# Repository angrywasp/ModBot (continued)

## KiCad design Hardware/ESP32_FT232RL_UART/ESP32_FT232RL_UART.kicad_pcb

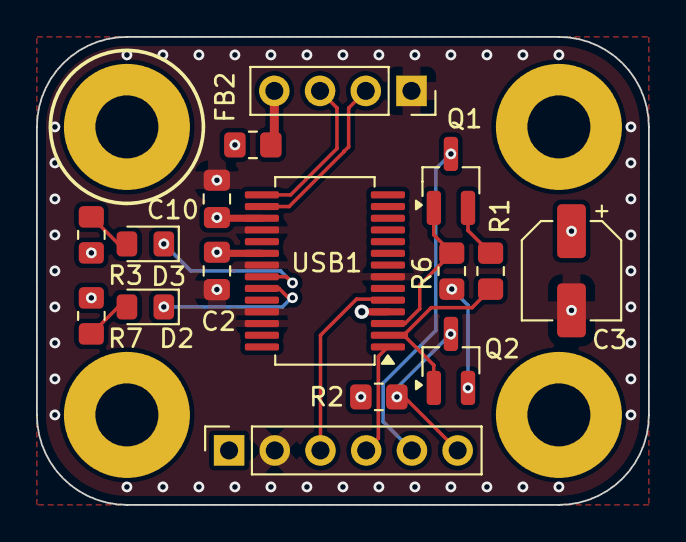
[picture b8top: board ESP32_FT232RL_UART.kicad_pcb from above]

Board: 4 copper layers, 34.0 x 26.0 mm, 16 parts (0 on the bottom side), 18 nets.

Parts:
C2, C10: 0.1uF; C_0805_2012Metric_Pad1.18x1.45mm_HandSolder
C3: 47uF; CP_Elec_5x5.3
D2: BLUE; LED_0805_2012Metric_Pad1.15x1.40mm_HandSolder
D3: RED; LED_0805_2012Metric_Pad1.15x1.40mm_HandSolder
FB2: 220; R_0805_2012Metric_Pad1.20x1.40mm_HandSolder
J1: Conn_01x06; PinSocket_1x06_P2.54mm_Vertical
J2: Conn_01x04; PinSocket_1x04_P2.54mm_Vertical
Q1, Q2: NPN; SOT-23_Handsoldering
R1, R2, R6: 10k; R_0805_2012Metric_Pad1.20x1.40mm_HandSolder
R3, R7: 330; R_0805_2012Metric_Pad1.20x1.40mm_HandSolder
USB1: FT232L; SSOP-28_5.3x10.2mm_P0.65mm

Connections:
+3.3V: C10.2, R2.2, USB1.4 (VCCIO), USB1.17 (3V3OUT)
+5V: C2.2, C3.1, FB2.2, J1.1, R3.1, R7.2, USB1.20 (VCC)
DTR: Q2.1 (E), R1.1, USB1.2 (DTR)
EN: J1.5, Q1.3 (C)
GND: C2.1, C3.2, C10.1, J1.2, J2.1, USB1.7 (GND), USB1.18 (GND), USB1.21 (GND), USB1.25 (AGND), USB1.26 (TEST)
IO0: J1.6, Q2.3 (C), R2.1
unnamed: D2.2 (A), R7.1
unnamed: D2.1 (K), USB1.23 (CBUS0)
unnamed: D3.2 (A), R3.2
unnamed: D3.1 (K), USB1.22 (CBUS1)
unnamed: FB2.1, J2.4
unnamed: Q1.2 (B), R1.2
unnamed: Q2.2 (B), R6.2
RTS: Q1.1 (E), R6.1, USB1.3 (RTS)
RXD: J1.3, USB1.5 (RXD)
TXD: J1.4, USB1.1 (TXD)
USB+: J2.3, USB1.15 (USBD+)
USB-: J2.2, USB1.16 (USBD-)

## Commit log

2026-05-19 Add Kicad symbols and footprints
2026-05-19 Clean up schematics a bit
2026-05-19 Add new hardware module
2026-05-19 Remove GCC as a submodule
2026-05-19 Pull GCC path from an environment variable
2026-05-19 build script improvements
2026-05-19 Fix include path
2026-05-19 More of the same
2026-05-19 More petty updates
2026-05-19 Finally fixed the build script
2026-05-25 Hardware updates and cleanup
2026-06-25 Hardware updates. Add Lr04 lora module datasheets
